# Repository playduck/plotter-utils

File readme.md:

# plotter-utils

A playground to interact with a [Roland DXY-1150 Plotter](datasheets/DXY-1150A.pdf).

This repository provides a script to interface with the plotter and output generated HPGL files over RS-232.

Make sure the plotter's DIP switches are configured correctly before using!

## RS-232 Serial Communication

The Plotter uses the [RS-232-**C**](datasheets/EIA_RS-232-C.pdf) implementation.
This requires much greater voltage levels than modern transmitters are capable of producing.
The [MAX3232](datasheets/MAX3232.pdf) is compliant and can be used for this.

The script as of right now sends and waits a set period.
This can cause the plotters internal buffer to overflow.
Apparently reading the remaining buffer capacity does not work (at least not reliably).
Ways to fix this issue:
1. (Hacky) Make sure the outbound data rate is slow enough. This is achieved by increasing the command delay `-d` flag.
2. (Recommended) Use RS-232 Handshaking and only output data, once CTS is active (This behavior should be handled by hardware). Note: The CTS signal has the same voltage level requirements as the RX/TX lines. This solution requires dedicated hardware.

## HPGL Generation

HPGL can be generated by various programs:
- KiCad offers an HPGL exporter
- [vpype](https://github.com/abey79/vpype) and its various plugins offer a vast selection of tools
- DIY, just write HPGL by hand, it's fun :)

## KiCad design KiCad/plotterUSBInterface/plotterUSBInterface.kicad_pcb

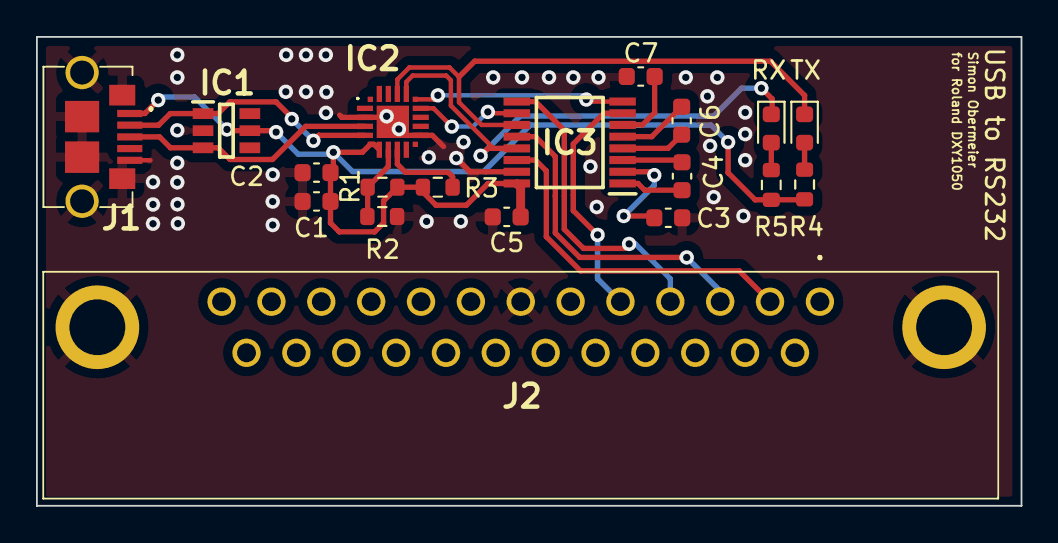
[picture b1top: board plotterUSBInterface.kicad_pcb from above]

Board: 2 copper layers, 54.7 x 26.0 mm, 19 parts (0 on the bottom side), 22 nets.

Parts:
C1: 4.7u; C_0603_1608Metric
C2, C5: 0.1u; C_0603_1608Metric
C3, C6, C7: 330n; C_0603_1608Metric
C4: 47n; C_0603_1608Metric
IC1: USBLC6-4SC6; SOT95P280X145-6N
IC2: CP2102N-A02-GQFN20; CP2102NA02GQFN20
IC3: MAX3232EUE+; SOP65P640X110-16N
J1: USB3075-30-A; USB307530A
J2: L717SDB25PA4CH3R
R1: 22.1k; R_0603_1608Metric
R2: 47.5k; R_0603_1608Metric
R3: 10k; R_0603_1608Metric
R4, R5: 470; R_0603_1608Metric
RX: RXD; LED_0603_1608Metric
TX: TXD; LED_0603_1608Metric

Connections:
+5V: C1.1, C2.1, C5.1, IC1.5 (VBUS), IC2.6 (VDD), IC2.7 (VREGIN), IC3.16 (VCC), J1.1 (VCC), R1.1, R3.2, R4.2, R5.2
CTS_Bridge: IC2.15 (CTS), IC3.10 (T2IN)
CTS_RS232: IC3.7 (T2OUT), J2.5
D+: IC1.3 (I/O2), IC2.4 (D+), J1.3 (D+)
D-: IC1.1 (I/O1), IC2.5 (D-), J1.2 (D-)
GND: C1.2, C2.2, C3.2, C5.2, C7.2, IC1.2 (GND), IC2.3 (GND_1), IC2.12 (GND_2), IC2.21 (EP_GND), IC3.15 (GND), J1.5 (GND), J1.MH1, J1.MH2, J1.MP1, J1.MP2, J1.MP3, J1.MP4, J2.7, J2.MH1, J2.MH2, R2.2
unnamed: C3.1, IC3.2 (V+)
unnamed: C4.1, IC3.1 (C1+)
unnamed: C4.2, IC3.3 (C1-)
unnamed: C6.1, IC3.4 (C2+)
unnamed: C6.2, IC3.5 (C2-)
unnamed: C7.1, IC3.6 (V-)
unnamed: R4.1, TX.2 (A)
unnamed: R5.1, RX.2 (A)
unnamed: IC2.8 (VBUS), R1.2, R2.1
unnamed: IC2.9 (RSTB), R3.1
RTS_Bridge: IC2.16 (RTS), IC3.8 (R2IN)
RTS_RS232: IC3.9 (R2OUT), J2.4
RX_Bridge: IC2.17 (RXD), IC3.13 (R1IN), RX.1 (K)
RX_RS232: IC3.12 (R1OUT), J2.3
TX_Bridge: IC2.18 (TXD), IC3.11 (T1IN), TX.1 (K)
TX_RS232: IC3.14 (T1OUT), J2.2

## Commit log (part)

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2022-04-08 Added datasheets
2022-04-08 Added KiCad Project
2022-04-08 Added library loader structure, Added Parts
2022-05-16 Simons PCB Version
2023-01-31 added vpype hpgl script and config
2023-01-31 various changes to plot py
2023-01-31 added dxy-1150 mainboard photos
2023-01-31 added readme
